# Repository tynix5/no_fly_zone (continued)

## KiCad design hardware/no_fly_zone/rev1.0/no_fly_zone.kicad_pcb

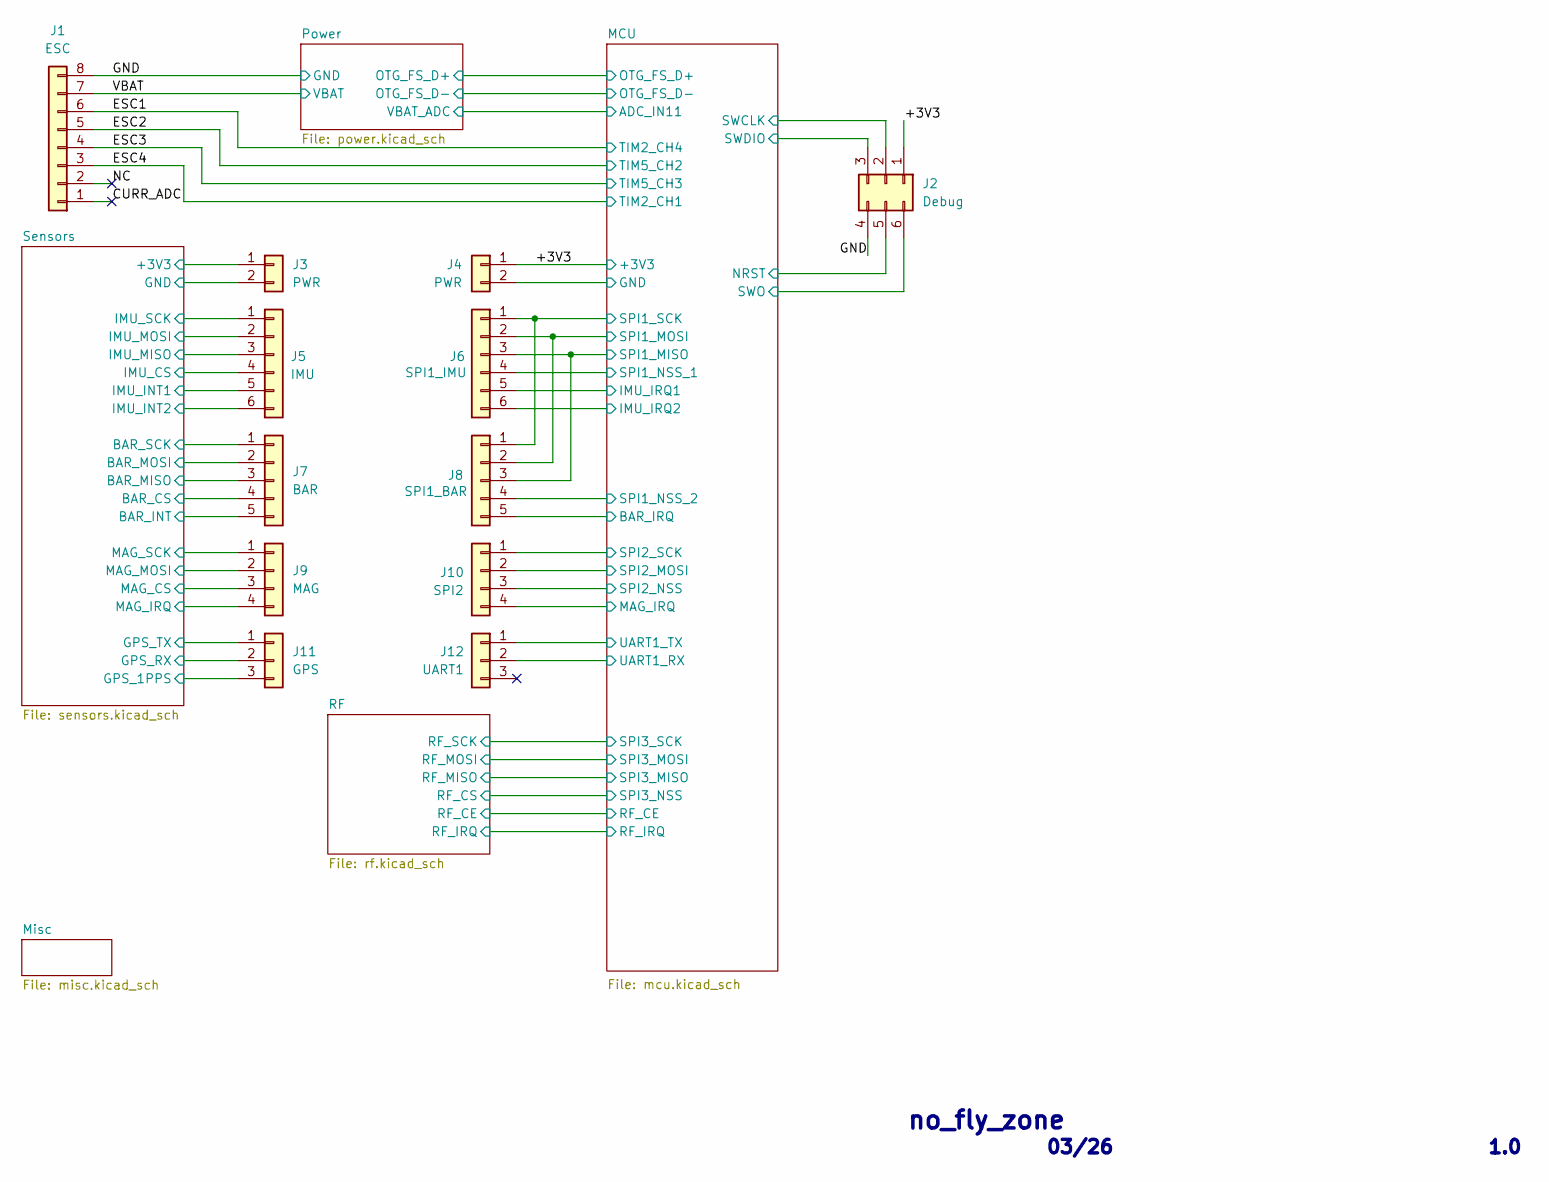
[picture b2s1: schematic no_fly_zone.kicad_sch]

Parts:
J1: ESC; JST_SH_SM08B-SRSS-TB_1x08-1MP_P1.00mm_Horizontal
J2: Debug; PinHeader_2x03_P2.54mm_Vertical
J3, J4: PWR; JST_SH_SM02B-SRSS-TB_1x02-1MP_P1.00mm_Horizontal
J5: IMU; JST_SH_SM06B-SRSS-TB_1x06-1MP_P1.00mm_Horizontal
J6: SPI1_IMU; JST_SH_SM06B-SRSS-TB_1x06-1MP_P1.00mm_Horizontal
J7: BAR; JST_SH_SM05B-SRSS-TB_1x05-1MP_P1.00mm_Horizontal
J8: SPI1_BAR; JST_SH_SM05B-SRSS-TB_1x05-1MP_P1.00mm_Horizontal
J9: MAG; JST_SH_SM04B-SRSS-TB_1x04-1MP_P1.00mm_Horizontal
J10: SPI2; JST_SH_SM04B-SRSS-TB_1x04-1MP_P1.00mm_Horizontal
J11: GPS; JST_SH_SM03B-SRSS-TB_1x03-1MP_P1.00mm_Horizontal
J12: UART1; JST_SH_SM03B-SRSS-TB_1x03-1MP_P1.00mm_Horizontal

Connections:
+3V3_MCU: J2.1, J4.1; also elsewhere on the board
+3V3_SENS: J3.1; also elsewhere on the board
/CURR_ADC: J1.1
/ESC1: J1.6; also elsewhere on the board
/ESC2: J1.5; also elsewhere on the board
/ESC3: J1.4; also elsewhere on the board
/ESC4: J1.3; also elsewhere on the board
/MCU/BAR_IRQ: J8.5; also elsewhere on the board
/MCU/IIS2_IRQ: J10.4; also elsewhere on the board
/MCU/IMU_IRQ1: J6.5; also elsewhere on the board
/MCU/IMU_IRQ2: J6.6; also elsewhere on the board
/MCU/NRST: J2.5; also elsewhere on the board
/MCU/SPI1_MISO: J6.3, J8.3; also elsewhere on the board
/MCU/SPI1_MOSI: J6.2, J8.2; also elsewhere on the board
/MCU/SPI1_NSS_1: J6.4; also elsewhere on the board
/MCU/SPI1_NSS_2: J8.4; also elsewhere on the board
/MCU/SPI1_SCK: J6.1, J8.1; also elsewhere on the board
/MCU/SPI2_MOSI: J10.2; also elsewhere on the board
/MCU/SPI2_NSS: J10.3; also elsewhere on the board
/MCU/SPI2_SCK: J10.1; also elsewhere on the board
/MCU/SWCLK: J2.2; also elsewhere on the board
/MCU/SWDIO: J2.3; also elsewhere on the board
/MCU/SWO: J2.6; also elsewhere on the board
/MCU/UART1_RX: J12.2; also elsewhere on the board
/MCU/UART1_TX: J12.1; also elsewhere on the board
/NC: J1.2
/Sensors/BAR_CS: J7.4; also elsewhere on the board
/Sensors/BAR_INT: J7.5; also elsewhere on the board
/Sensors/BAR_MISO: J7.3; also elsewhere on the board
/Sensors/BAR_MOSI: J7.2; also elsewhere on the board
/Sensors/BAR_SCK: J7.1; also elsewhere on the board
/Sensors/GPS_1PPS: J11.3; also elsewhere on the board
/Sensors/GPS_RX: J11.2; also elsewhere on the board
/Sensors/GPS_TX: J11.1; also elsewhere on the board
/Sensors/IMU_CS: J5.4; also elsewhere on the board
/Sensors/IMU_INT1: J5.5; also elsewhere on the board
/Sensors/IMU_INT2: J5.6; also elsewhere on the board
/Sensors/IMU_MISO: J5.3; also elsewhere on the board
/Sensors/IMU_MOSI: J5.2; also elsewhere on the board
/Sensors/IMU_SCK: J5.1; also elsewhere on the board
/Sensors/MAG_CS: J9.3; also elsewhere on the board
/Sensors/MAG_IRQ: J9.4; also elsewhere on the board
/Sensors/MAG_MOSI: J9.2; also elsewhere on the board
/Sensors/MAG_SCK: J9.1; also elsewhere on the board
GND_MCU: J1.8, J2.4, J4.2; also elsewhere on the board
GND_SENS: J3.2; also elsewhere on the board
VBAT: J1.7; also elsewhere on the board

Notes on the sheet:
no_fly_zone
1.0
03/26

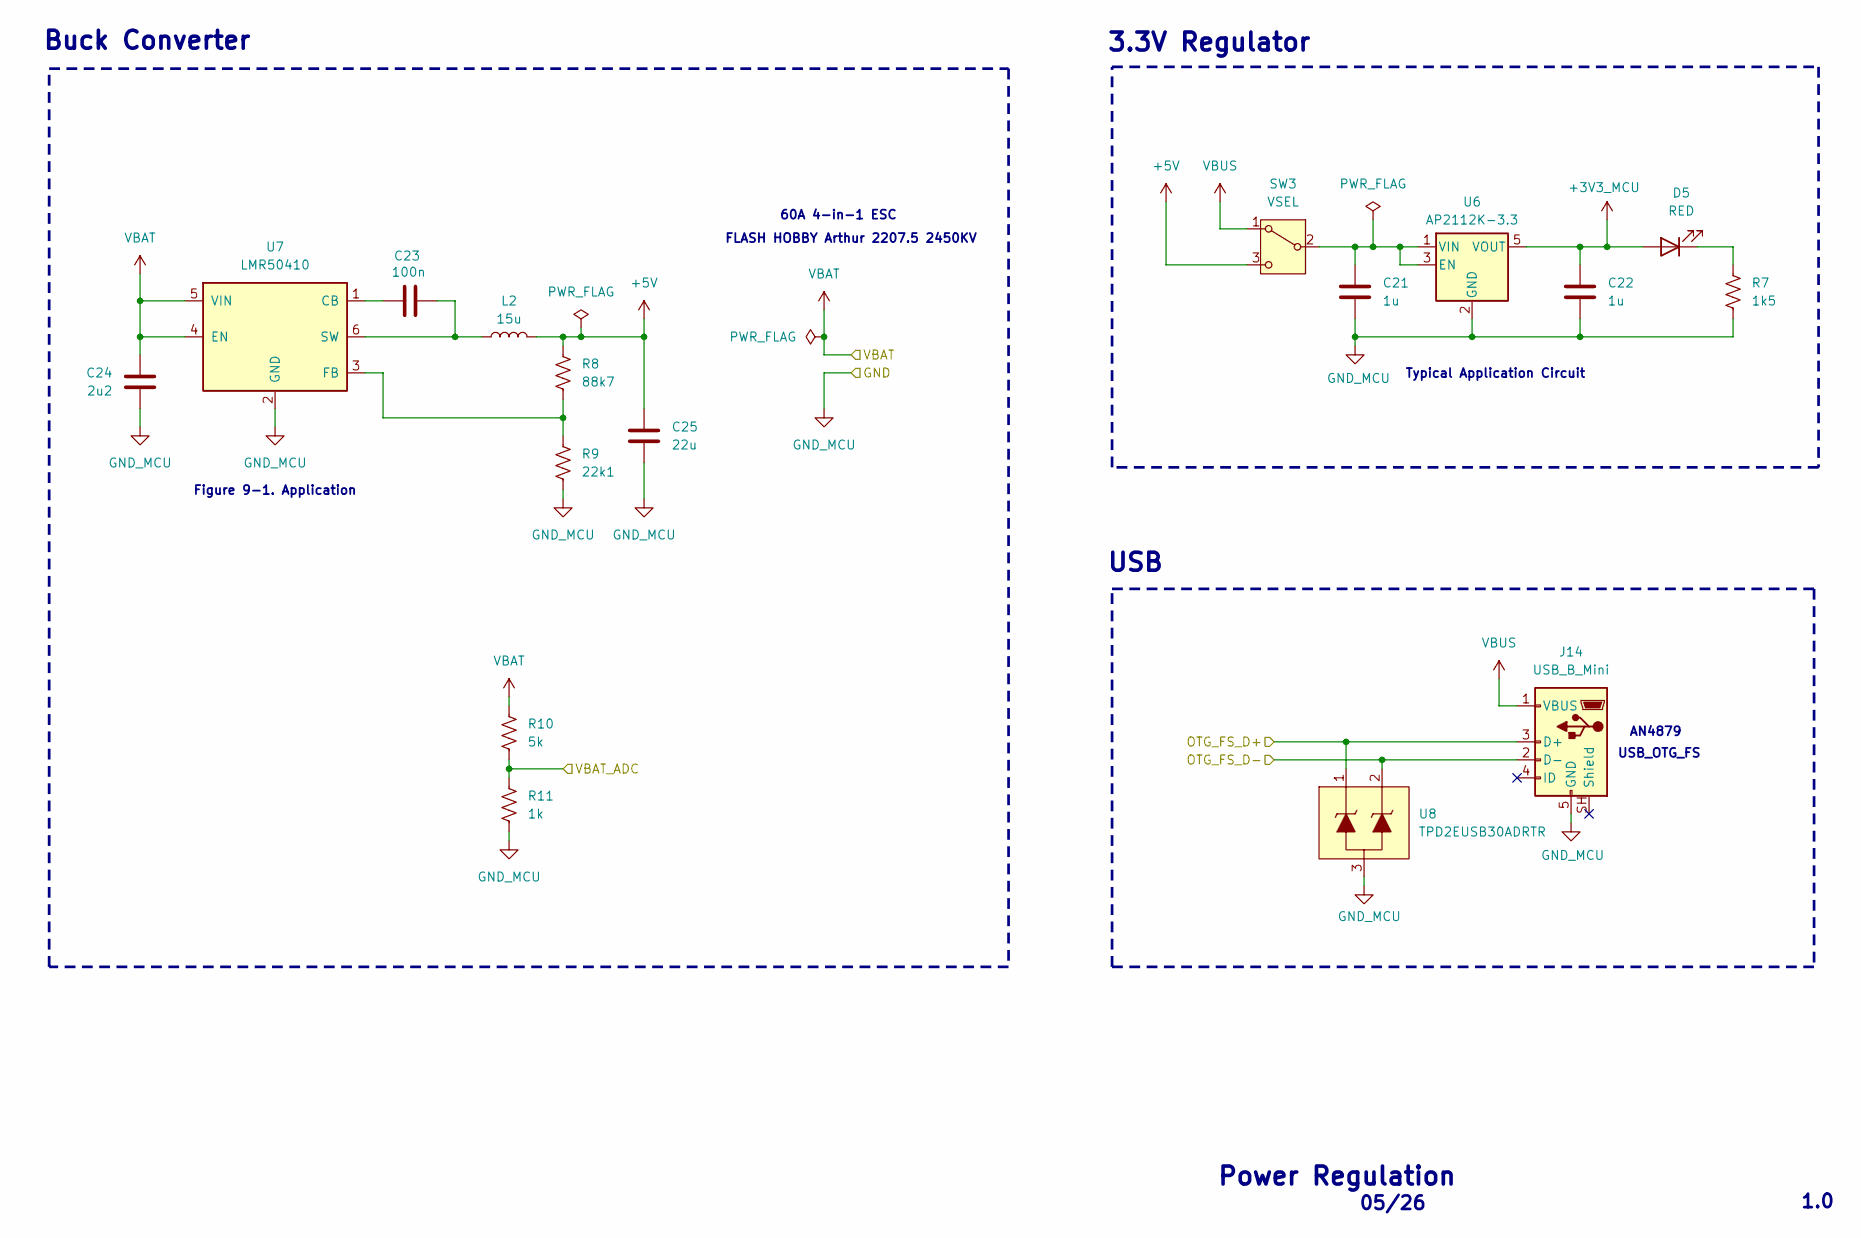
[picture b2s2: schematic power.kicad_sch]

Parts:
C21, C22: 1u; C_0805_2012Metric
C23: 100n; C_0805_2012Metric
C24: 2u2; C_0805_2012Metric
C25: 22u; C_0805_2012Metric
D5: RED; LED_0805_2012Metric
J14: USB_B_Mini; EDAC_690-005-299-043
L2: 15u; L_0805_2012Metric
R7: 1k5; R_0805_2012Metric
R8: 88k7; R_0805_2012Metric
R9: 22k1; R_0805_2012Metric
R10: 5k; R_0805_2012Metric
R11: 1k; R_0805_2012Metric
SW3: VSEL; SW_SPDT_PCM12
U6: AP2112K-3.3; SOT-23-5
U7: LMR50410; SOT-23-6
U8: SOT-723

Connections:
+3V3_MCU: C22.1, D5.2 (A), U6.5 (VOUT); also elsewhere on the board
+5V: C25.1, L2.2, R8.1, SW3.3 (C)
/MCU/ADC_IN11: R10.2, R11.1; also elsewhere on the board
/MCU/OTG_FS_D+: J14.3 (D+), U8.1; also elsewhere on the board
/MCU/OTG_FS_D-: J14.2 (D-), U8.2; also elsewhere on the board
GND_MCU: C21.2, C22.2, C24.2, C25.2, J14.5 (GND), R7.2, R9.2, R11.2, U6.2 (GND), U7.2 (GND), U8.3; also elsewhere on the board
unnamed: D5.1 (K), R7.1
unnamed: C21.1, SW3.2 (B), U6.1 (VIN), U6.3 (EN)
unnamed: C23.1, U7.1 (CB)
unnamed: R8.2, R9.1, U7.3 (FB)
unnamed: C23.2, L2.1, U7.6 (SW)
VBAT: C24.1, R10.1, U7.4 (EN), U7.5 (VIN); also elsewhere on the board
VBUS: J14.1 (VBUS), SW3.1 (A)

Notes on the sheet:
USB
Figure 9-1. Application
USB_OTG_FS
60A 4-in-1 ESC
FLASH HOBBY Arthur 2207.5 2450KV
05/26
AN4879
Buck Converter
Power Regulation
3.3V Regulator
1.0
Typical Application Circuit

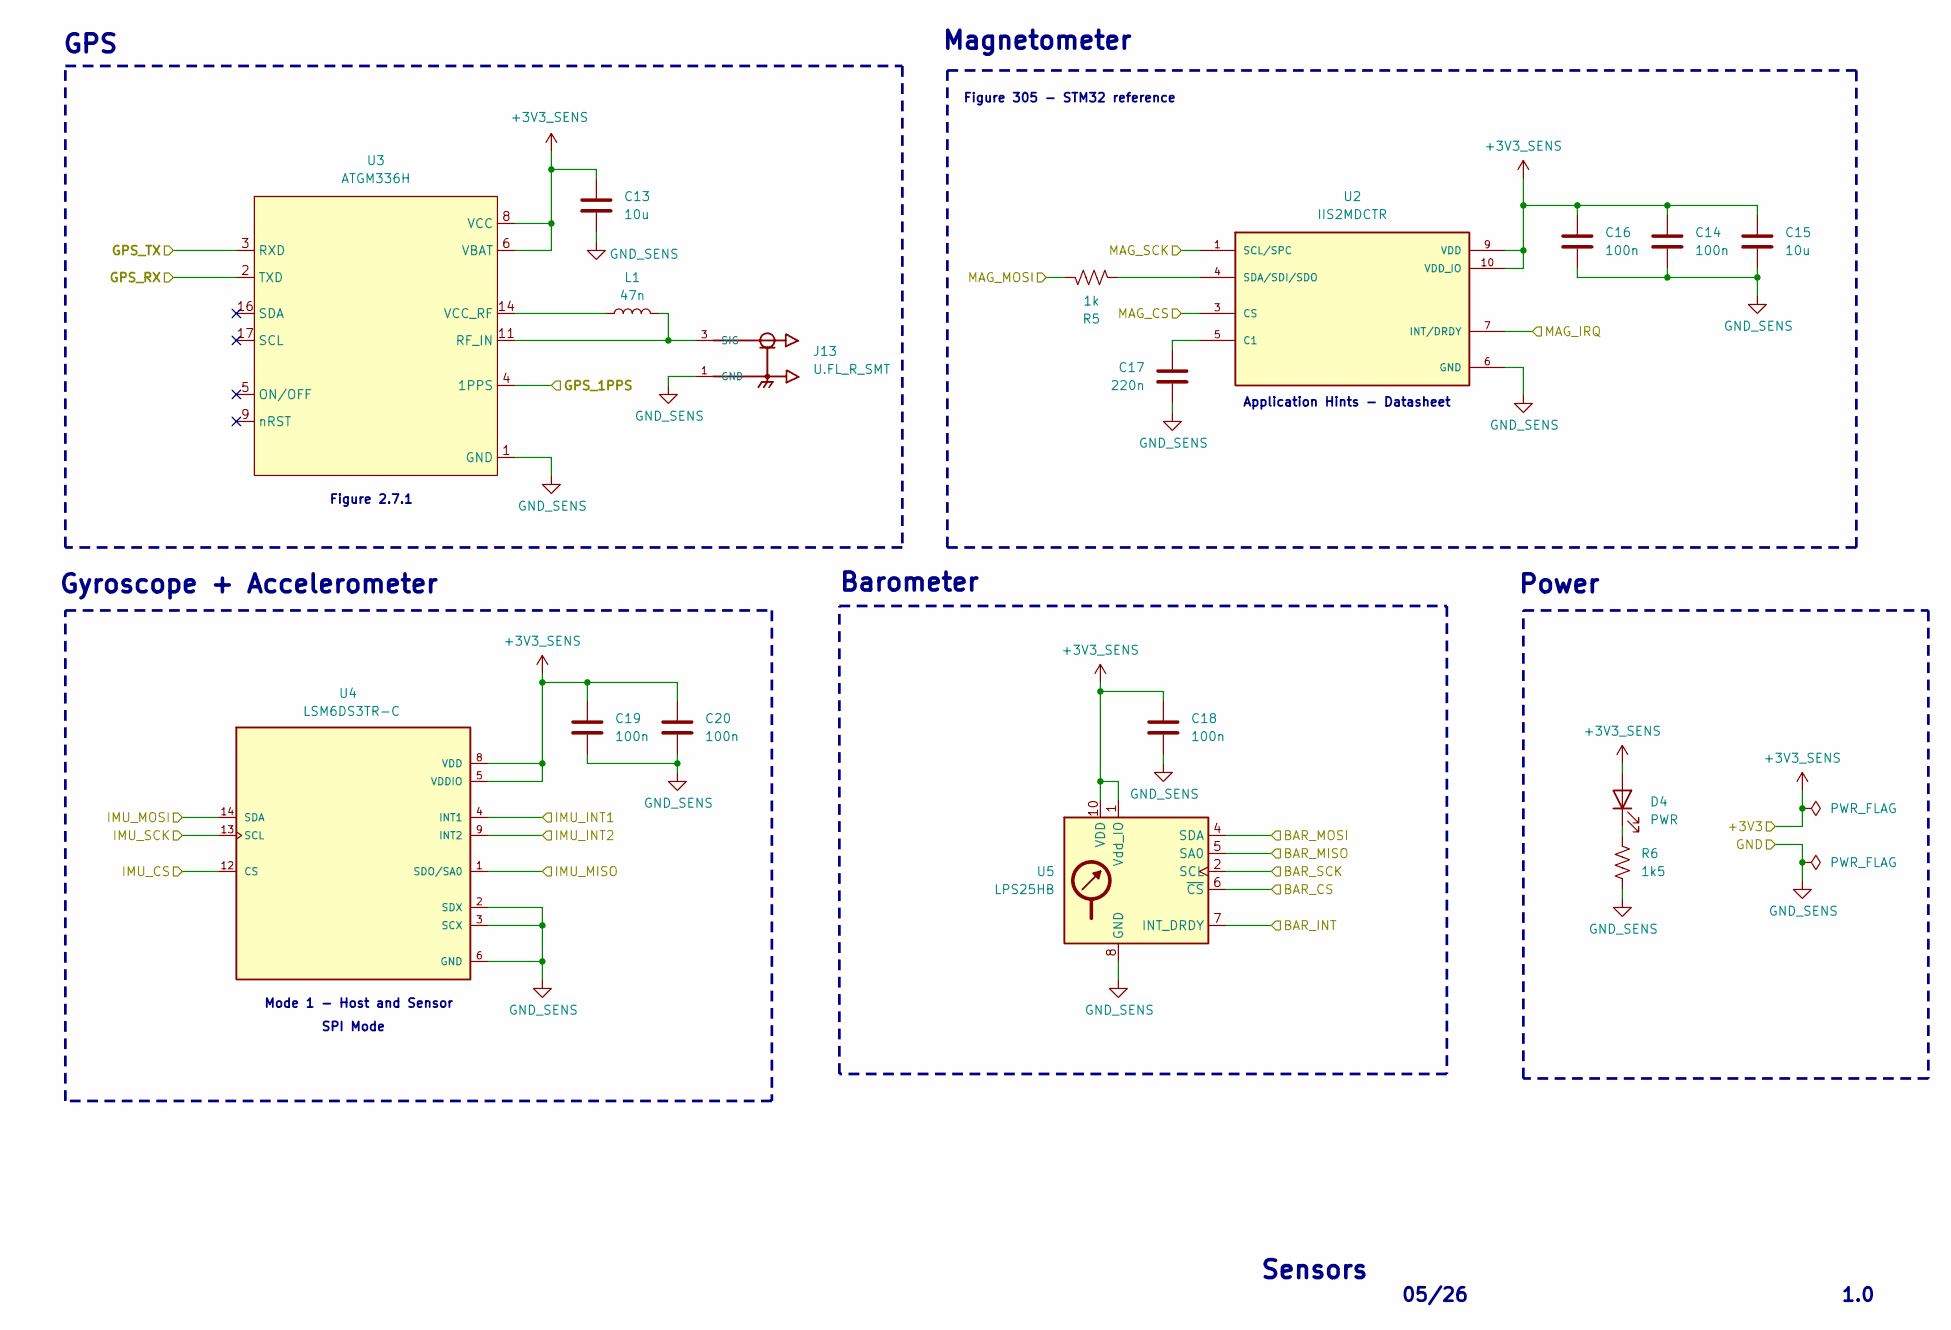
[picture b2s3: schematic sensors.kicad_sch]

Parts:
C13, C15: 10u; C_0805_2012Metric
C14, C16, C18, C19, C20: 100n; C_0805_2012Metric
C17: 220n; C_0805_2012Metric
D4: PWR; LED_0805_2012Metric
J13: U.FL_R_SMT; HRS_UFL_R_SMT
L1: 47n; L_0805_2012Metric
R5: 1k; R_0805_2012Metric
R6: 1k5; R_0805_2012Metric
U2: IIS2MDCTR; MOUSER_PART_NUMBER 511-IIS2MDCTR
U3: ATGM336H
U4: LSM6DS3TR-C; LSM6DS3TR
U5: LPS25HB; ST_HLGA-10_2.5x2.5mm_P0.6mm_LayoutBorder3x2y

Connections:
+3V3_SENS: C13.1, C14.1, C15.1, C16.1, C18.1, C19.1, C20.1, D4.2 (A), U2.9 (VDD), U2.10 (VDD_IO), U3.6 (VBAT), U3.8 (VCC), U4.5 (VDDIO), U4.8 (VDD), U5.1 (Vdd_IO), U5.10 (VDD); also elsewhere on the board
/Sensors/BAR_CS: U5.6 (~CS); also elsewhere on the board
/Sensors/BAR_INT: U5.7 (INT_DRDY); also elsewhere on the board
/Sensors/BAR_MISO: U5.5 (SA0); also elsewhere on the board
/Sensors/BAR_MOSI: U5.4 (SDA); also elsewhere on the board
/Sensors/BAR_SCK: U5.2 (SCL); also elsewhere on the board
/Sensors/GPS_1PPS: U3.4 (1PPS); also elsewhere on the board
/Sensors/GPS_RX: U3.2 (TXD); also elsewhere on the board
/Sensors/GPS_TX: U3.3 (RXD); also elsewhere on the board
/Sensors/IMU_CS: U4.12 (CS); also elsewhere on the board
/Sensors/IMU_INT1: U4.4 (INT1); also elsewhere on the board
/Sensors/IMU_INT2: U4.9 (INT2); also elsewhere on the board
/Sensors/IMU_MISO: U4.1 (SDO/SA0); also elsewhere on the board
/Sensors/IMU_MOSI: U4.14 (SDA); also elsewhere on the board
/Sensors/IMU_SCK: U4.13 (SCL); also elsewhere on the board
/Sensors/MAG_CS: U2.3 (CS); also elsewhere on the board
/Sensors/MAG_IRQ: U2.7 (INT/DRDY); also elsewhere on the board
/Sensors/MAG_MOSI: R5.1; also elsewhere on the board
/Sensors/MAG_SCK: U2.1 (SCL/SPC); also elsewhere on the board
GND_SENS: C13.2, C14.2, C15.2, C16.2, C17.2, C18.2, C19.2, C20.2, J13.1 (GND), J13.2 (GND), R6.2, U2.6 (GND), U2.8 (GND), U3.1 (GND), U3.10 (GND), U3.12 (GND), U4.2 (SDX), U4.3 (SCX), U4.6 (GND), U4.7 (GND), U5.3 (GND), U5.8 (GND), U5.9 (GND); also elsewhere on the board
unnamed: D4.1 (K), R6.1
unnamed: J13.3 (SIG), L1.1, U3.11 (RF_IN)
unnamed: C17.1, U2.5 (C1)
unnamed: R5.2, U2.4 (SDA/SDI/SDO)
unnamed: L1.2, U3.14 (VCC_RF)

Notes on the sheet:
SPI Mode
Barometer
05/26
GPS
Figure 305 - STM32 reference
Mode 1 - Host and Sensor
1.0
Application Hints - Datasheet
Gyroscope + Accelerometer
Power
Magnetometer
Figure 2.7.1
Sensors

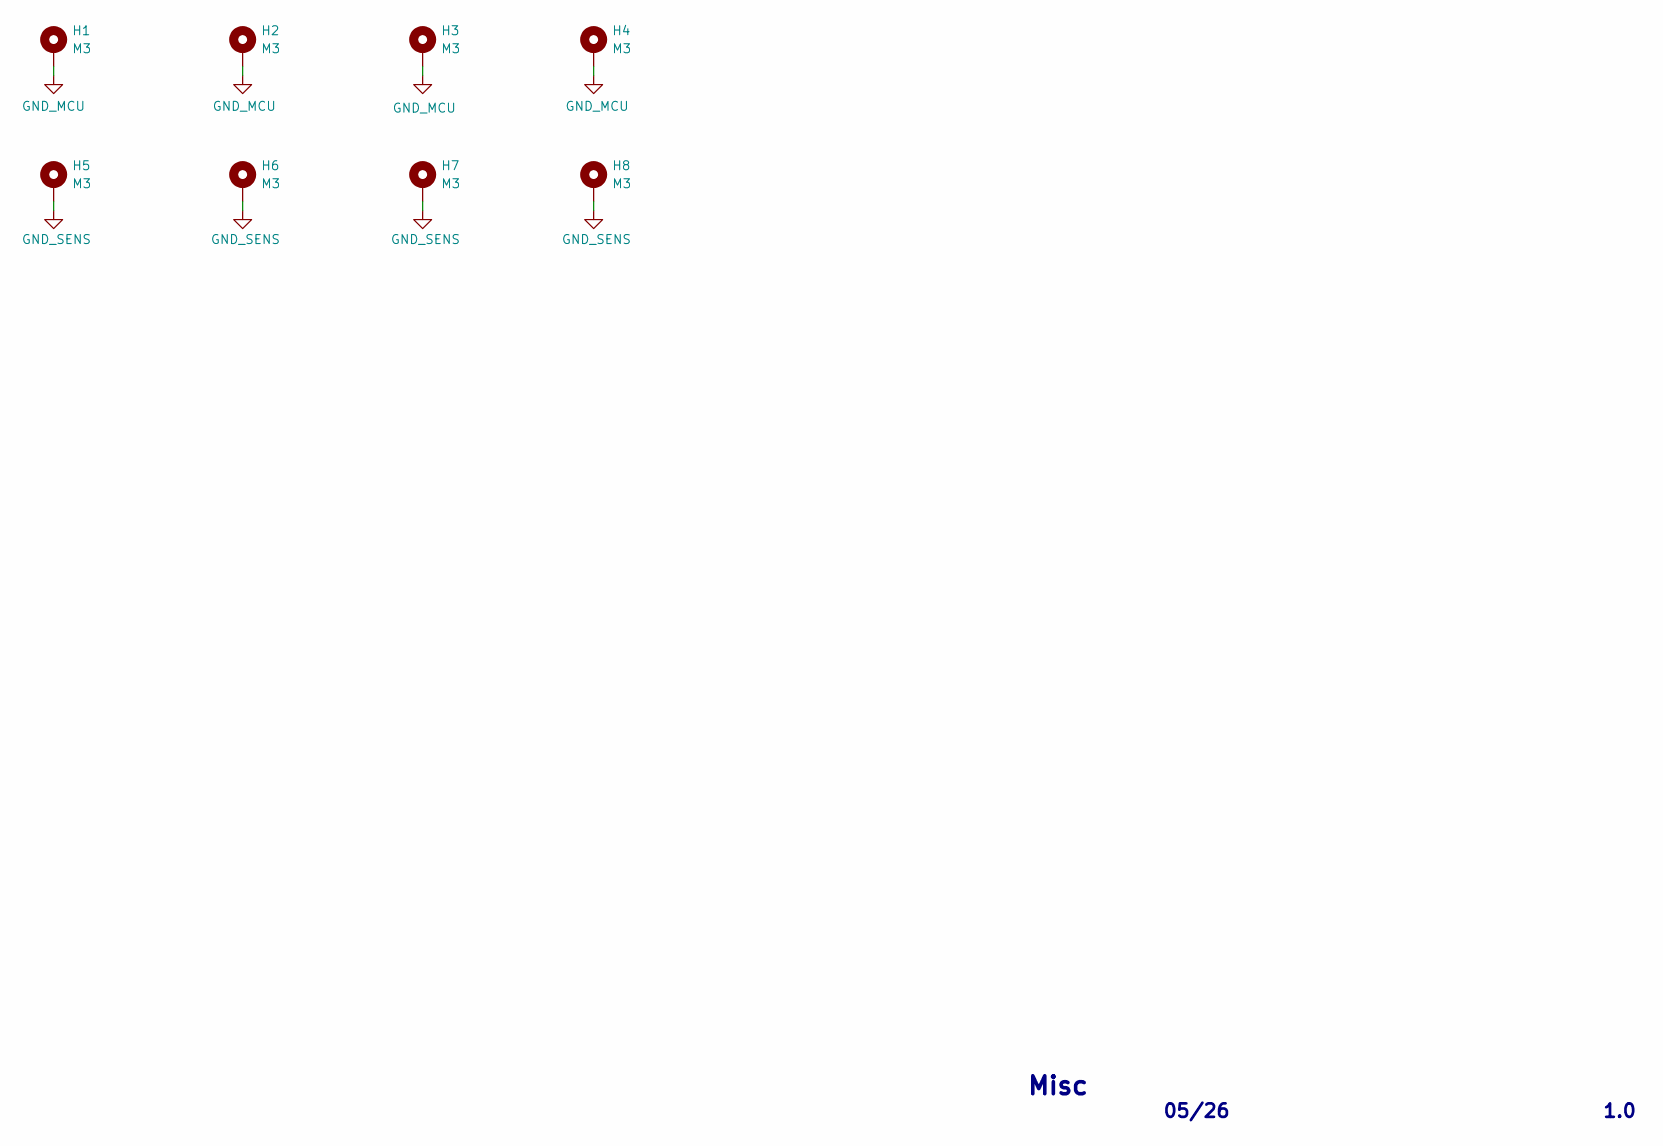
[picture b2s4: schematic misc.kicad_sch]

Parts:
H1, H2, H3, H4, H5, H6, H7, H8: M3; MountingHole_3.2mm_M3_DIN965_Pad

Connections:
GND_MCU: H1.1 (1_1), H2.1 (1_1), H3.1 (1_1), H4.1 (1_1); also elsewhere on the board
GND_SENS: H5.1 (1_1), H6.1 (1_1), H7.1 (1_1), H8.1 (1_1); also elsewhere on the board

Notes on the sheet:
05/26
1.0
Misc

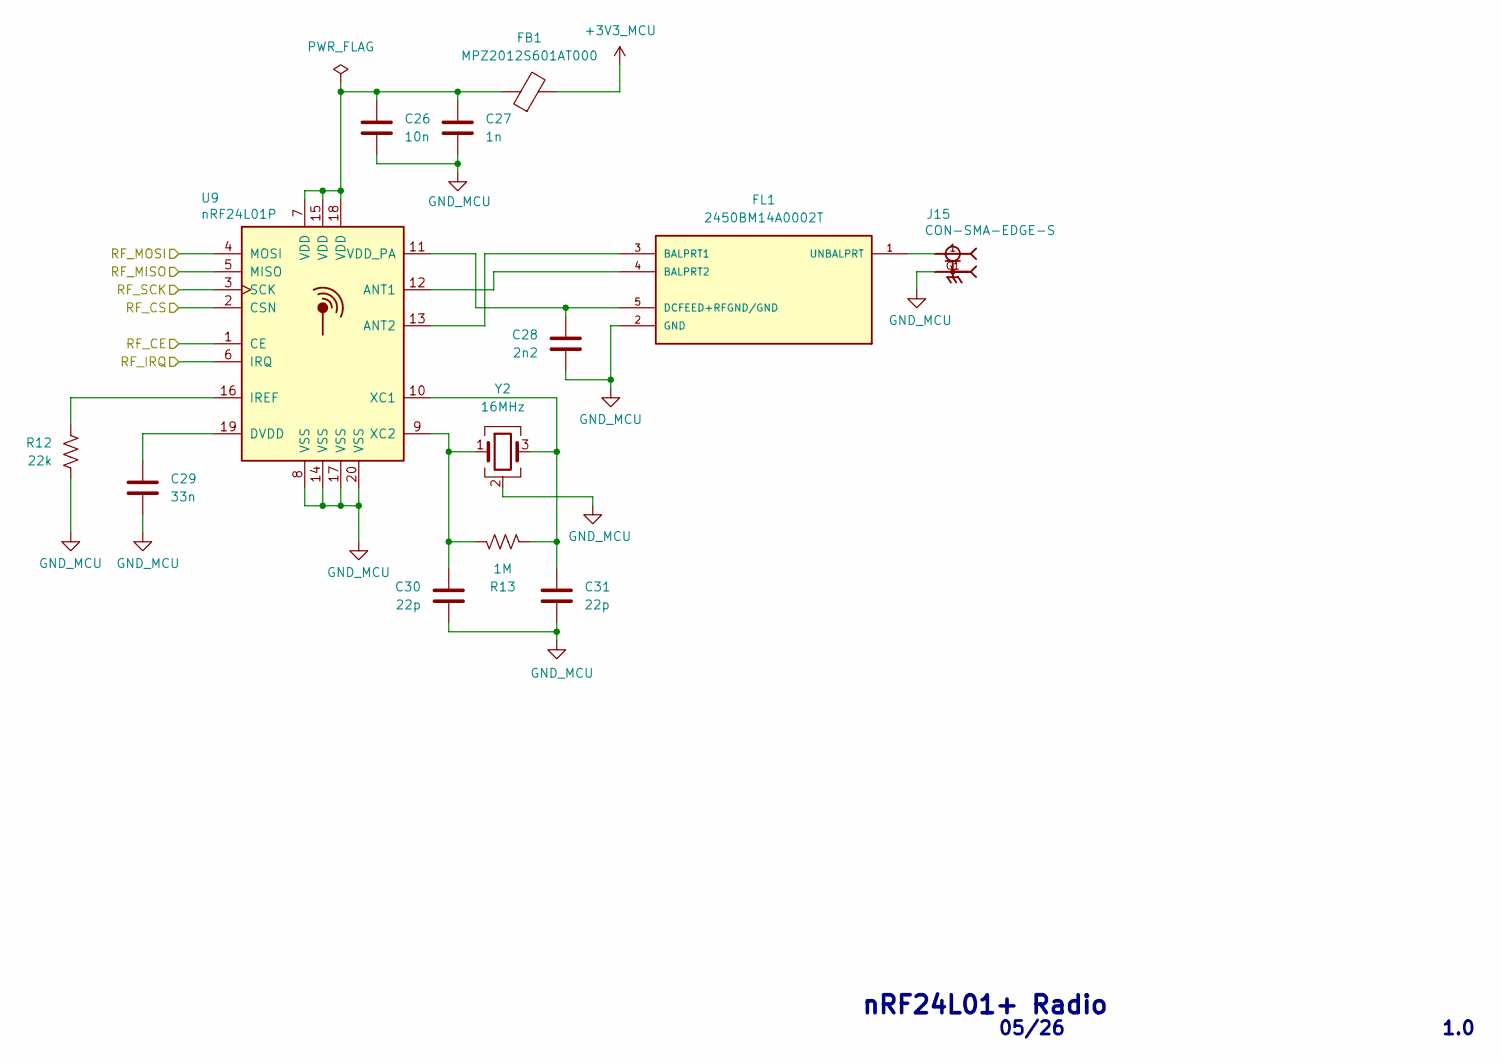
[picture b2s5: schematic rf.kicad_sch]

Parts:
C26: 10n; C_0402_1005Metric
C27: 1n; C_0402_1005Metric
C28: 2n2; C_0402_1005Metric
C29: 33n; C_0402_1005Metric
C30, C31: 22p; C_0402_1005Metric
FB1: MPZ2012S601AT000; R_0805_2012Metric
FL1: 2450BM14A0002T; FIL_2450BM14A0002T
J15: CON-SMA-EDGE-S; RFSOLUTIONS_CON-SMA-EDGE-S
R12: 22k; R_0402_1005Metric
R13: 1M; R_0402_1005Metric
U9: nRF24L01P; QFN-20-1EP_4x4mm_P0.5mm_EP2.5x2.5mm
Y2: 16MHz; XTAL_ABM8AIG-16.000MHZ-12-2Z-T3

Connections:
+3V3_MCU: FB1.2; also elsewhere on the board
/MCU/RF_CE: U9.1 (CE); also elsewhere on the board
/MCU/RF_IRQ: U9.6 (IRQ); also elsewhere on the board
/MCU/SPI3_MISO: U9.5 (MISO); also elsewhere on the board
/MCU/SPI3_MOSI: U9.4 (MOSI); also elsewhere on the board
/MCU/SPI3_NSS: U9.2 (CSN); also elsewhere on the board
/MCU/SPI3_SCK: U9.3 (SCK); also elsewhere on the board
GND_MCU: C26.2, C27.2, C28.2, C29.2, C30.2, C31.2, FL1.2 (GND), J15.G1, J15.G2, J15.G3, J15.G4, R12.2, U9.8 (VSS), U9.14 (VSS), U9.17 (VSS), U9.20 (VSS), Y2.2 (G), Y2.4 (G); also elsewhere on the board
unnamed: C26.1, C27.1, FB1.1, U9.7 (VDD), U9.15 (VDD), U9.18 (VDD)
unnamed: FL1.3 (BALPRT1), U9.13 (ANT2)
unnamed: FL1.4 (BALPRT2), U9.12 (ANT1)
unnamed: C28.1, FL1.5 (DCFEED+RFGND/GND), U9.11 (VDD_PA)
unnamed: FL1.1 (UNBALPRT), J15.1
unnamed: C29.1, U9.19 (DVDD)
unnamed: R12.1, U9.16 (IREF)
unnamed: C31.1, R13.1, U9.10 (XC1), Y2.3
unnamed: C30.1, R13.2, U9.9 (XC2), Y2.1

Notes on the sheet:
1.0
nRF24L01+ Radio
05/26

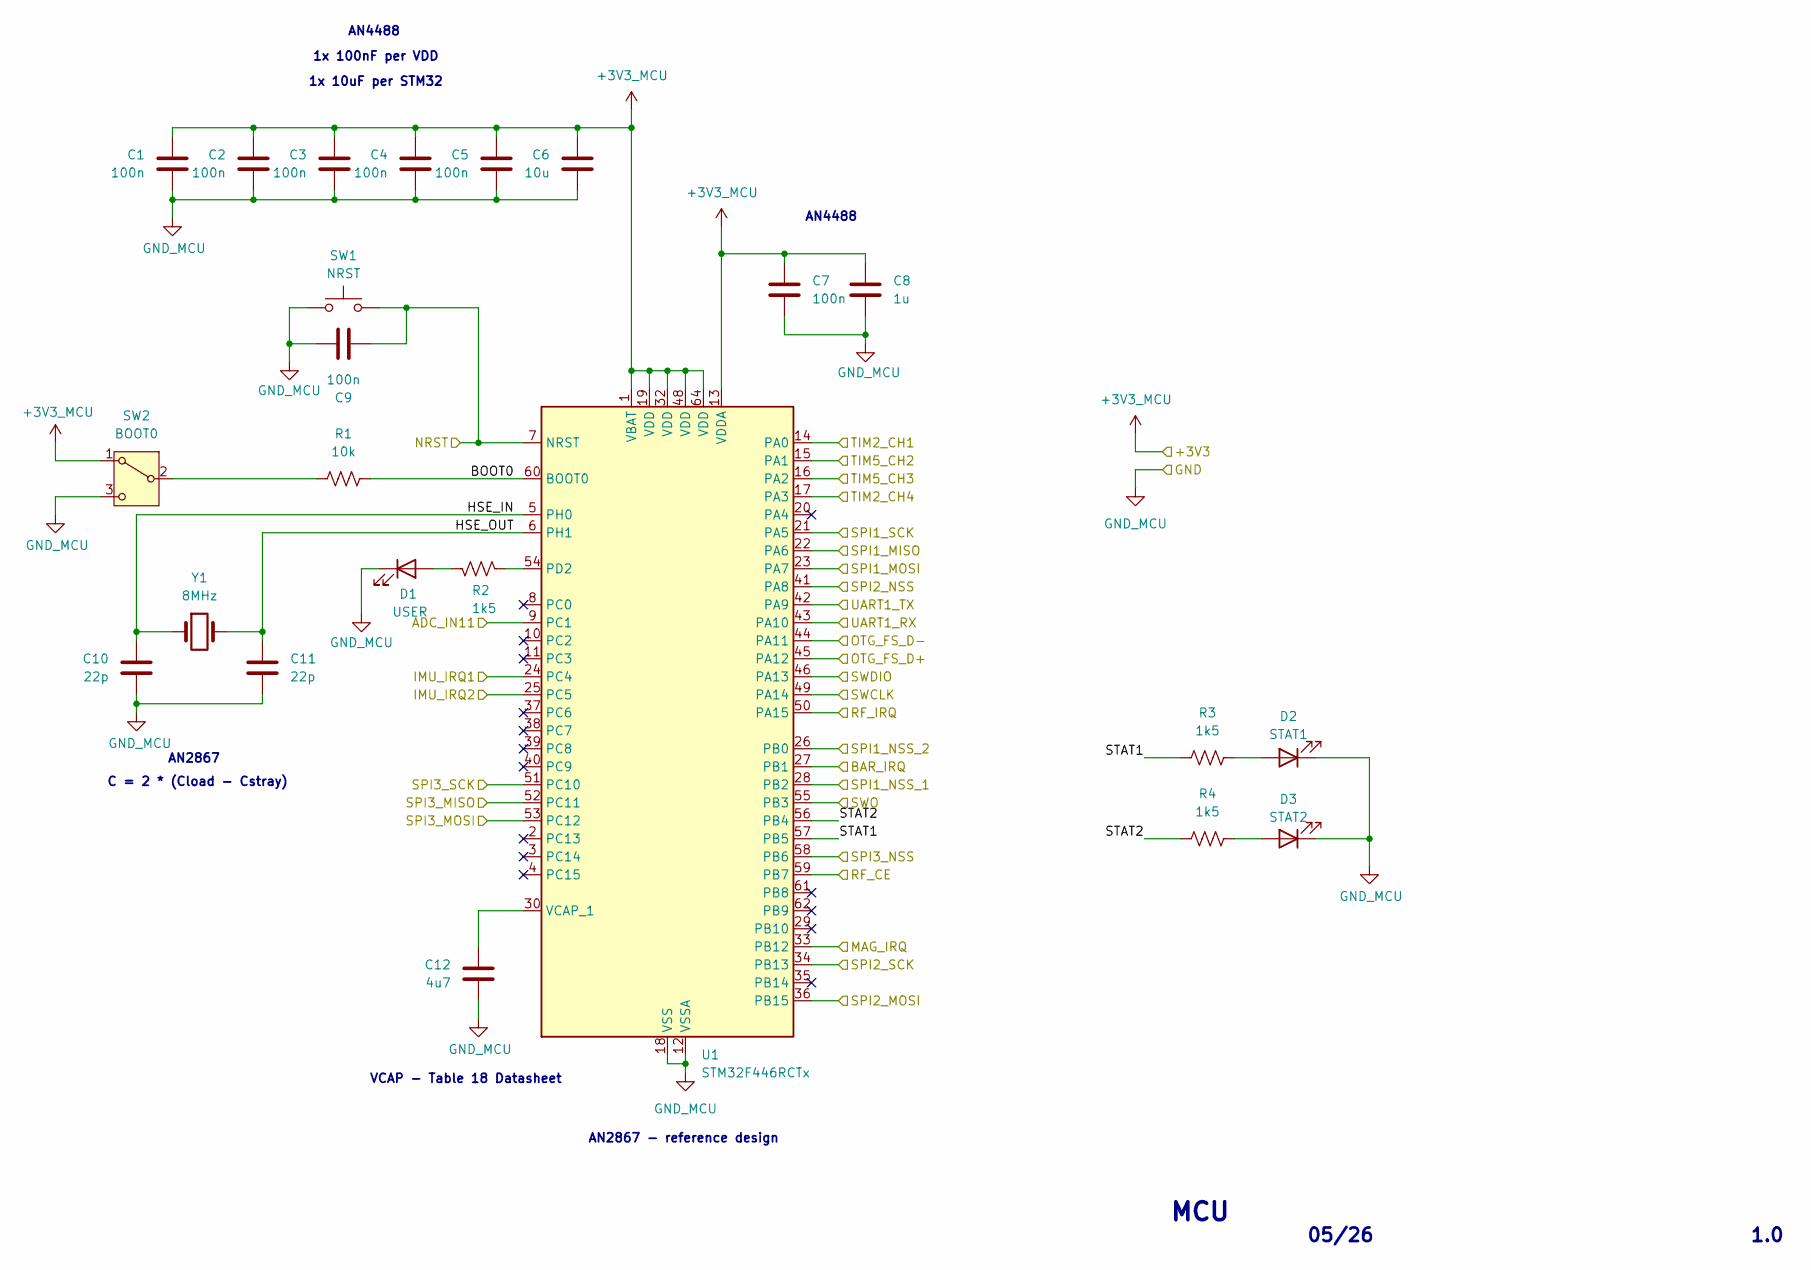
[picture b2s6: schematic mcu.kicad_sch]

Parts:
C1, C2, C3, C4, C5, C7, C9: 100n; C_0805_2012Metric
C6: 10u; C_0805_2012Metric
C8: 1u; C_0805_2012Metric
C10, C11: 22p; C_0805_2012Metric
C12: 4u7; C_0805_2012Metric
D1: USER; LED_0805_2012Metric
D2: STAT1; LED_0805_2012Metric
D3: STAT2; LED_0805_2012Metric
R1: 10k; R_0805_2012Metric
R2, R3, R4: 1k5; R_0805_2012Metric
SW1: NRST; SW_SPST_TL3305A
SW2: BOOT0; SW_SPDT_PCM12
U1: STM32F446RCTx; LQFP-64_10x10mm_P0.5mm
Y1: 8MHz; XTAL_ABM3-16.000MHZ-D2Y-T

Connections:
+3V3_MCU: C1.1, C2.1, C3.1, C4.1, C5.1, C6.1, C7.1, C8.1, SW2.1 (A), U1.1 (VBAT), U1.13 (VDDA), U1.19 (VDD), U1.32 (VDD), U1.48 (VDD), U1.64 (VDD); also elsewhere on the board
/ESC1: U1.17 (PA3); also elsewhere on the board
/ESC2: U1.16 (PA2); also elsewhere on the board
/ESC3: U1.15 (PA1); also elsewhere on the board
/ESC4: U1.14 (PA0); also elsewhere on the board
/MCU/ADC_IN11: U1.9 (PC1); also elsewhere on the board
/MCU/BAR_IRQ: U1.27 (PB1); also elsewhere on the board
/MCU/BOOT0: R1.2, U1.60 (BOOT0)
/MCU/HSE_IN: C10.1, U1.5 (PH0), Y1.1
/MCU/HSE_OUT: C11.1, U1.6 (PH1), Y1.2
/MCU/IIS2_IRQ: U1.33 (PB12); also elsewhere on the board
/MCU/IMU_IRQ1: U1.24 (PC4); also elsewhere on the board
/MCU/IMU_IRQ2: U1.25 (PC5); also elsewhere on the board
/MCU/NRST: C9.1, SW1.2, U1.7 (NRST); also elsewhere on the board
/MCU/OTG_FS_D+: U1.45 (PA12); also elsewhere on the board
/MCU/OTG_FS_D-: U1.44 (PA11); also elsewhere on the board
/MCU/RF_CE: U1.59 (PB7); also elsewhere on the board
/MCU/RF_IRQ: U1.50 (PA15); also elsewhere on the board
/MCU/SPI1_MISO: U1.22 (PA6); also elsewhere on the board
/MCU/SPI1_MOSI: U1.23 (PA7); also elsewhere on the board
/MCU/SPI1_NSS_1: U1.28 (PB2); also elsewhere on the board
/MCU/SPI1_NSS_2: U1.26 (PB0); also elsewhere on the board
/MCU/SPI1_SCK: U1.21 (PA5); also elsewhere on the board
/MCU/SPI2_MOSI: U1.36 (PB15); also elsewhere on the board
/MCU/SPI2_NSS: U1.41 (PA8); also elsewhere on the board
/MCU/SPI2_SCK: U1.34 (PB13); also elsewhere on the board
/MCU/SPI3_MISO: U1.52 (PC11); also elsewhere on the board
/MCU/SPI3_MOSI: U1.53 (PC12); also elsewhere on the board
/MCU/SPI3_NSS: U1.58 (PB6); also elsewhere on the board
/MCU/SPI3_SCK: U1.51 (PC10); also elsewhere on the board
/MCU/STAT1: R3.1, U1.57 (PB5)
/MCU/STAT2: R4.1, U1.56 (PB4)
/MCU/SWCLK: U1.49 (PA14); also elsewhere on the board
/MCU/SWDIO: U1.46 (PA13); also elsewhere on the board
/MCU/SWO: U1.55 (PB3); also elsewhere on the board
/MCU/UART1_RX: U1.43 (PA10); also elsewhere on the board
/MCU/UART1_TX: U1.42 (PA9); also elsewhere on the board
GND_MCU: C1.2, C2.2, C3.2, C4.2, C5.2, C6.2, C7.2, C8.2, C9.2, C10.2, C11.2, C12.2, D1.1 (K), D2.1 (K), D3.1 (K), SW1.1, SW2.3 (C), U1.12 (VSSA), U1.18 (VSS), U1.31 (VSS), U1.47 (VSS), U1.63 (VSS); also elsewhere on the board
unnamed: D1.2 (A), R2.2
unnamed: D2.2 (A), R3.2
unnamed: D3.2 (A), R4.2
unnamed: R1.1, SW2.2 (B)
unnamed: R2.1, U1.54 (PD2)
unnamed: C12.1, U1.30 (VCAP_1)

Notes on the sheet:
AN4488
1x 100nF per VDD
1.0
MCU
05/26
VCAP - Table 18 Datasheet
AN2867 - reference design
1x 10uF per STM32
C = 2 * (Cload - Cstray)
AN2867

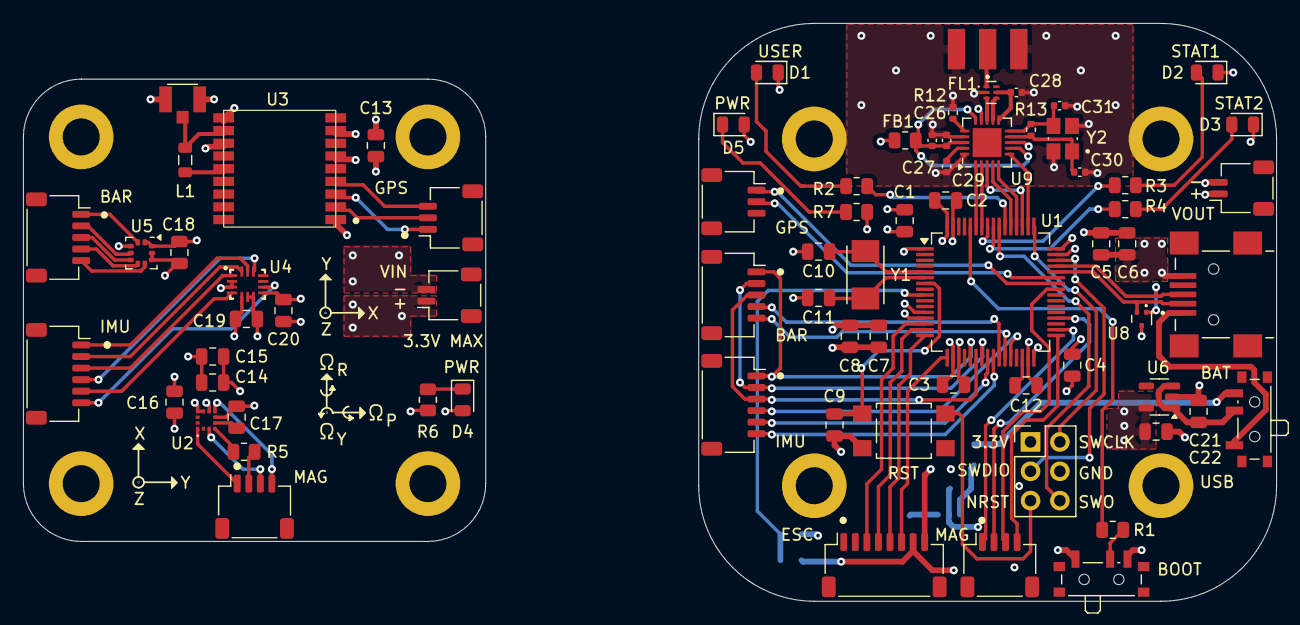
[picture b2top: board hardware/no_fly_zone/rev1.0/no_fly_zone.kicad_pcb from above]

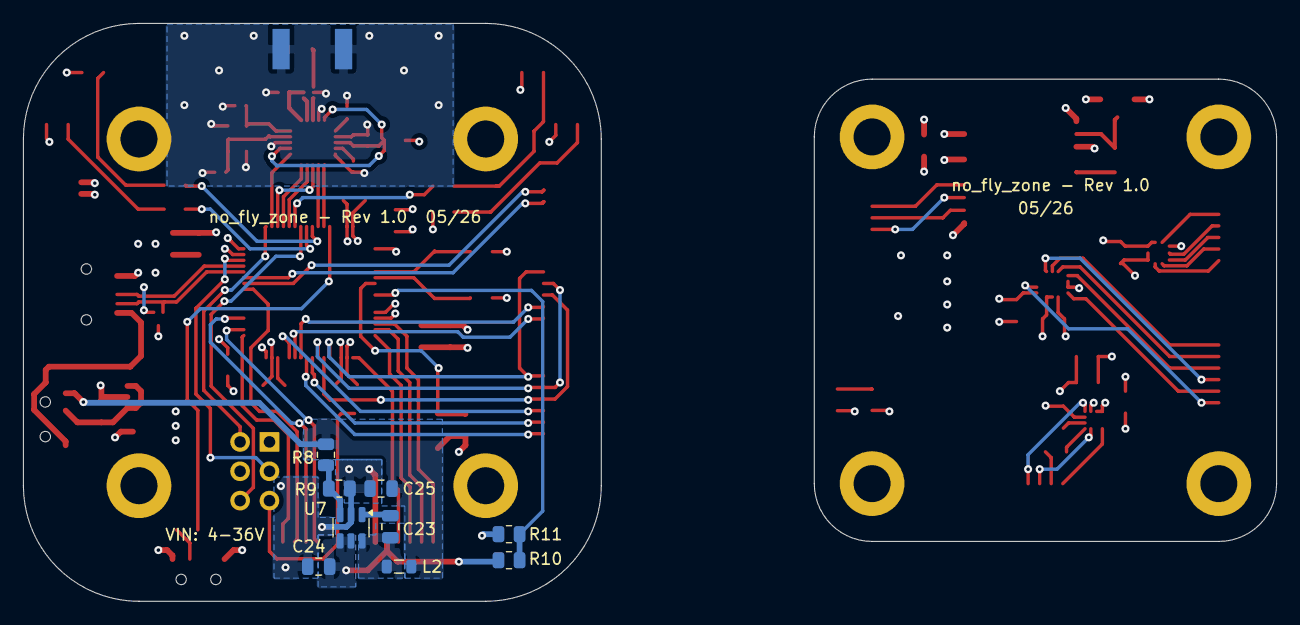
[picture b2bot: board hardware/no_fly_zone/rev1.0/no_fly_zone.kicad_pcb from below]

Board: 4 copper layers, 108.4 x 50.0 mm, 90 parts (9 on the bottom side), 86 nets.
